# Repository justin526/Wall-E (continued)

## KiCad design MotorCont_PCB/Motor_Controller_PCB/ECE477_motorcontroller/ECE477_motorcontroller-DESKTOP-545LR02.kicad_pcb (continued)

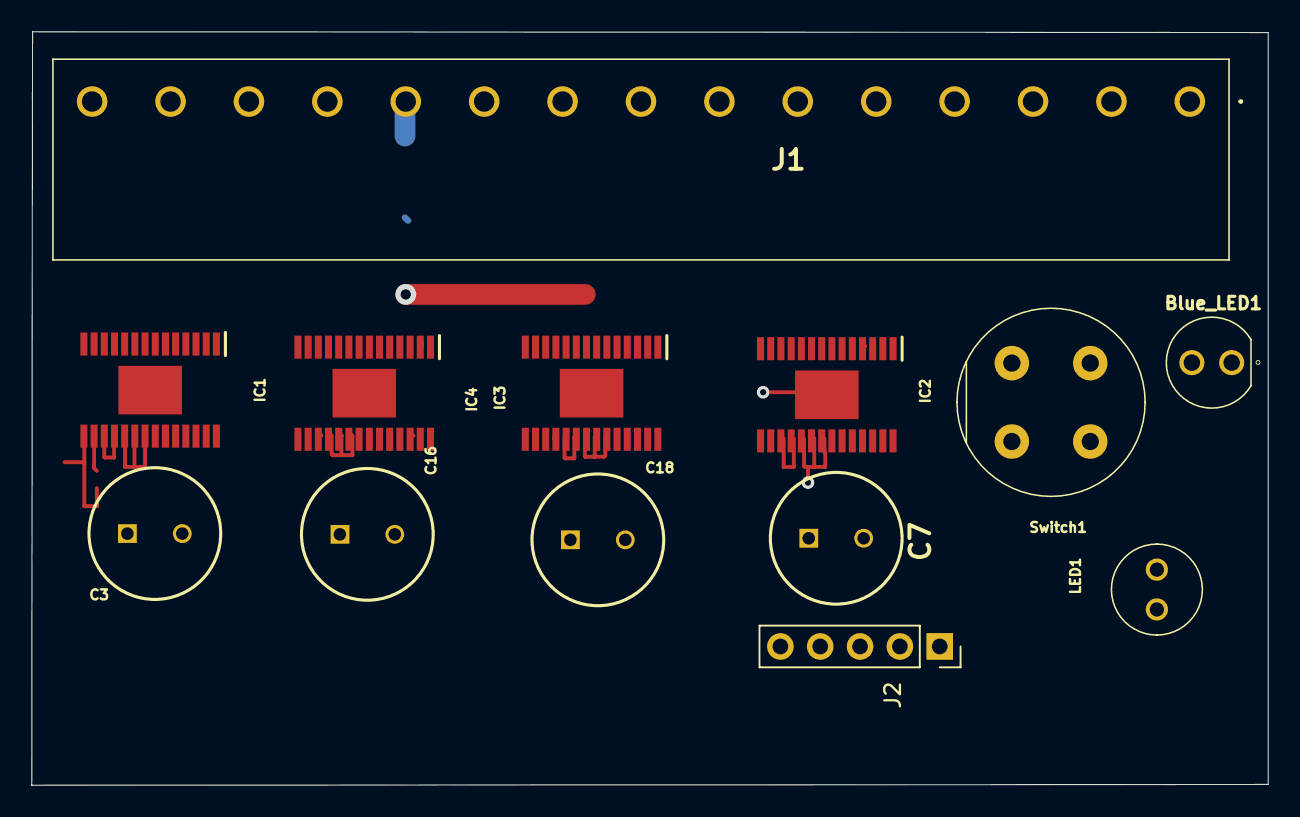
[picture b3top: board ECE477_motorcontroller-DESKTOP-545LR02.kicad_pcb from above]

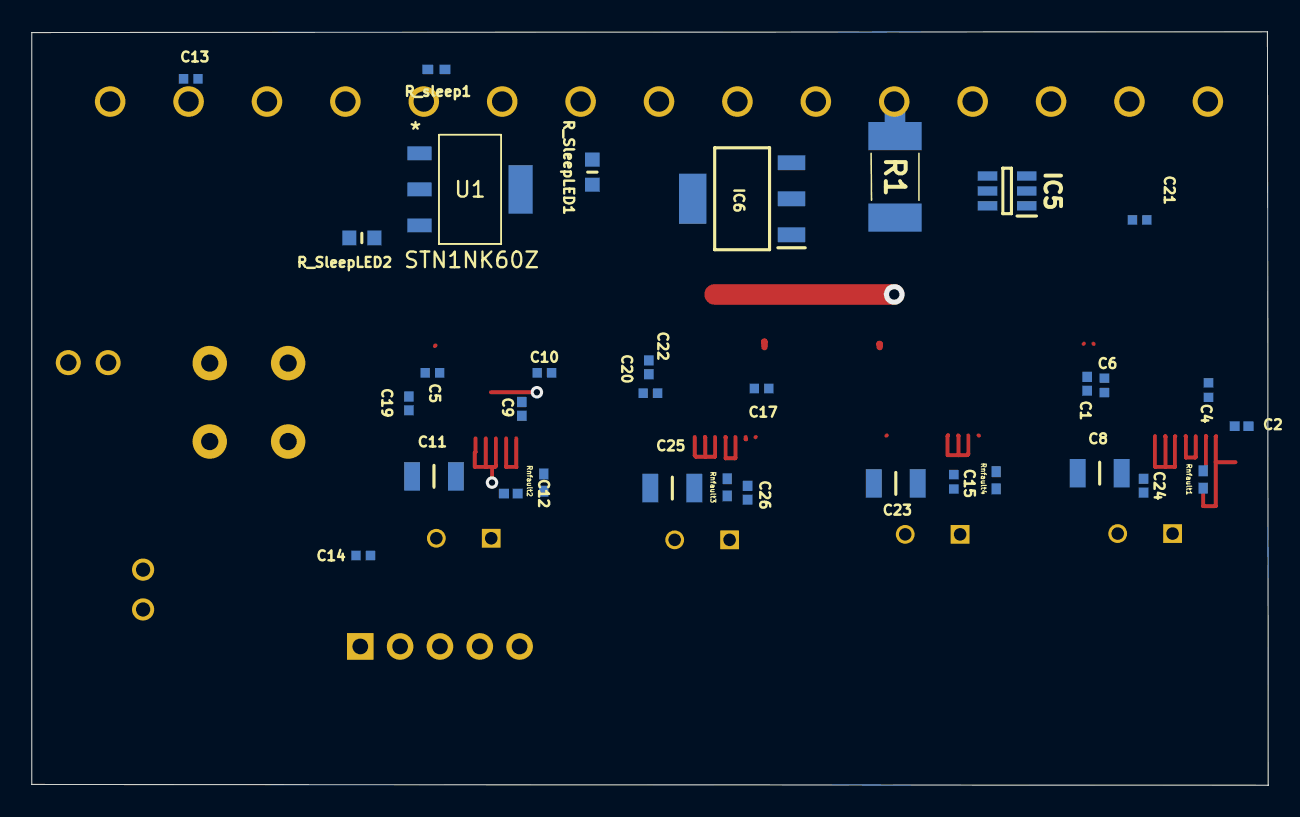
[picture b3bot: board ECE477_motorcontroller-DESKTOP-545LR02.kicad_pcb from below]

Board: 4 copper layers, 78.8 x 48.0 mm, 46 parts (33 on the bottom side), 43 nets.

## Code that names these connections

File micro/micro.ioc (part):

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Mcu.Name=STM32F446Z(C-E)Tx
Mcu.Package=LQFP144
Mcu.UserName=STM32F446ZETx
PA10.Mode=Asynchronous
PA10.Signal=USART1_RX
PA6.Signal=GPIO_Output
PA9.Mode=Asynchronous
PA9.Signal=USART1_TX
PB10.Mode=Asynchronous
PB10.Signal=USART3_TX
PB4.Signal=S_TIM3_CH1
PB5.Signal=S_TIM3_CH2
PB8.Signal=S_TIM2_CH1_ETR
PB9.Signal=S_TIM2_CH2
PC5.Mode=Asynchronous
PC5.Signal=USART3_RX
PE2.Signal=GPIO_Output
PE3.Signal=GPIO_Output
PE4.Signal=GPIO_Output
PE5.Signal=GPIO_Output
PE6.Signal=GPIO_Output
PE7.Mode=Asynchronous
PE7.Signal=UART5_RX
PE8.Mode=Asynchronous
PE8.Signal=UART5_TX
PF5.Signal=GPIO_Output
PF7.Mode=IN5
PF7.Signal=ADC3_IN5
RCC.SYSCLKFreq_VALUE=16000000
board=custom

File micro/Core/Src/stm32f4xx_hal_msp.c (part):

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
    __HAL_RCC_GPIOF_CLK_ENABLE();
    /**ADC3 GPIO Configuration
    PF7     ------> ADC3_IN5
    */
    GPIO_InitStruct.Pin = GPIO_PIN_7;
    GPIO_InitStruct.Mode = GPIO_MODE_ANALOG;
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    __HAL_RCC_ADC3_CLK_DISABLE();

    /**ADC3 GPIO Configuration
    PF7     ------> ADC3_IN5
    */
    HAL_GPIO_DeInit(GPIOF, GPIO_PIN_7);

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  /* USER CODE END TIM2_MspPostInit 0 */
    __HAL_RCC_GPIOB_CLK_ENABLE();
    /**TIM2 GPIO Configuration
    PB8     ------> TIM2_CH1
    PB9     ------> TIM2_CH2
    */
    GPIO_InitStruct.Pin = GPIO_PIN_8|GPIO_PIN_9;
    GPIO_InitStruct.Mode = GPIO_MODE_AF_PP;
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
    __HAL_RCC_GPIOB_CLK_ENABLE();
    /**TIM3 GPIO Configuration
    PB4     ------> TIM3_CH1
    PB5     ------> TIM3_CH2
    */
    GPIO_InitStruct.Pin = GPIO_PIN_4|GPIO_PIN_5;
    GPIO_InitStruct.Mode = GPIO_MODE_AF_PP;
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
    __HAL_RCC_GPIOE_CLK_ENABLE();
    /**UART5 GPIO Configuration
    PE7     ------> UART5_RX
    PE8     ------> UART5_TX
    */
    GPIO_InitStruct.Pin = GPIO_PIN_7|GPIO_PIN_8;
    GPIO_InitStruct.Mode = GPIO_MODE_AF_PP;
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
    __HAL_RCC_GPIOA_CLK_ENABLE();
    /**USART1 GPIO Configuration
    PA9     ------> USART1_TX
    PA10     ------> USART1_RX
    */
    GPIO_InitStruct.Pin = GPIO_PIN_9|GPIO_PIN_10;
    GPIO_InitStruct.Mode = GPIO_MODE_AF_PP;
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    __HAL_RCC_GPIOC_CLK_ENABLE();
    __HAL_RCC_GPIOB_CLK_ENABLE();
    /**USART3 GPIO Configuration
    PC5     ------> USART3_RX
    PB10     ------> USART3_TX
    */
    GPIO_InitStruct.Pin = GPIO_PIN_5;
    GPIO_InitStruct.Mode = GPIO_MODE_AF_PP;
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    __HAL_RCC_UART5_CLK_DISABLE();

    /**UART5 GPIO Configuration
    PE7     ------> UART5_RX
    PE8     ------> UART5_TX
    */
    HAL_GPIO_DeInit(GPIOE, GPIO_PIN_7|GPIO_PIN_8);

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    __HAL_RCC_USART1_CLK_DISABLE();

    /**USART1 GPIO Configuration
    PA9     ------> USART1_TX
    PA10     ------> USART1_RX
    */
    HAL_GPIO_DeInit(GPIOA, GPIO_PIN_9|GPIO_PIN_10);

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    __HAL_RCC_USART3_CLK_DISABLE();

    /**USART3 GPIO Configuration
    PC5     ------> USART3_RX
    PB10     ------> USART3_TX
    */
    HAL_GPIO_DeInit(GPIOC, GPIO_PIN_5);

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
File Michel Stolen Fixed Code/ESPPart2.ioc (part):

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Mcu.Name=STM32F407V(E-G)Tx
Mcu.Package=LQFP100
Mcu.UserName=STM32F407VGTx
PA0-WKUP.GPIOParameters=GPIO_PuPd,GPIO_Label,GPIO_ModeDefaultEXTI
PA0-WKUP.GPIO_Label=B1 [Blue PushButton]
PA0-WKUP.GPIO_ModeDefaultEXTI=GPIO_MODE_EVT_RISING
PA0-WKUP.GPIO_PuPd=GPIO_NOPULL
PA0-WKUP.Signal=GPXTI0
PA10.GPIOParameters=GPIO_Speed,GPIO_PuPd,GPIO_Label,GPIO_Mode
PA10.GPIO_Label=OTG_FS_ID
PA10.GPIO_Mode=GPIO_MODE_AF_PP
PA10.GPIO_PuPd=GPIO_NOPULL
PA10.GPIO_Speed=GPIO_SPEED_FREQ_LOW
PA10.Signal=USB_OTG_FS_ID
PA11.GPIOParameters=GPIO_Speed,GPIO_PuPd,GPIO_Label,GPIO_Mode
PA11.GPIO_Label=OTG_FS_DM
PA11.GPIO_Mode=GPIO_MODE_AF_PP
PA11.GPIO_PuPd=GPIO_NOPULL
PA11.GPIO_Speed=GPIO_SPEED_FREQ_LOW
PA11.Signal=USB_OTG_FS_DM
PA12.GPIOParameters=GPIO_Speed,GPIO_PuPd,GPIO_Label,GPIO_Mode
PA12.GPIO_Label=OTG_FS_DP
PA12.GPIO_Mode=GPIO_MODE_AF_PP
PA12.GPIO_PuPd=GPIO_NOPULL
PA12.GPIO_Speed=GPIO_SPEED_FREQ_LOW
PA12.Signal=USB_OTG_FS_DP
PA13.GPIOParameters=GPIO_Label
PA13.GPIO_Label=SWDIO
PA13.Mode=Serial_Wire
PA13.Signal=SYS_JTMS-SWDIO
PA14.GPIOParameters=GPIO_Label
PA14.GPIO_Label=SWCLK
PA14.Mode=Serial_Wire
PA14.Signal=SYS_JTCK-SWCLK
PA2.Mode=Asynchronous
PA2.Signal=USART2_TX
PA3.Mode=Asynchronous
PA3.Signal=USART2_RX
PA4.GPIOParameters=GPIO_Speed,GPIO_PuPd,GPIO_Label,GPIO_Mode
PA4.GPIO_Label=I2S3_WS [CS43L22_LRCK]
PA4.GPIO_Mode=GPIO_MODE_AF_PP
PA4.GPIO_PuPd=GPIO_NOPULL
PA4.GPIO_Speed=GPIO_SPEED_FREQ_LOW
PA4.Signal=I2S3_WS
PA5.GPIOParameters=GPIO_Speed,GPIO_PuPd,GPIO_Label,GPIO_Mode
PA5.GPIO_Label=SPI1_SCK [LIS302DL_SCL/SPC]
PA5.GPIO_Mode=GPIO_MODE_AF_PP
PA5.GPIO_PuPd=GPIO_NOPULL
PA5.GPIO_Speed=GPIO_SPEED_FREQ_LOW
PA5.Signal=SPI1_SCK
PA6.GPIOParameters=GPIO_Speed,GPIO_PuPd,GPIO_Label,GPIO_Mode
PA6.GPIO_Label=SPI1_MISO [LIS302DL_SDO]
PA6.GPIO_Mode=GPIO_MODE_AF_PP
PA6.GPIO_PuPd=GPIO_NOPULL
PA6.GPIO_Speed=GPIO_SPEED_FREQ_LOW
PA6.Signal=SPI1_MISO
PA7.GPIOParameters=GPIO_Speed,GPIO_PuPd,GPIO_Label,GPIO_Mode
PA7.GPIO_Label=SPI1_MOSI [LIS302DL_SDA/SDI/SDO]
PA7.GPIO_Mode=GPIO_MODE_AF_PP
PA7.GPIO_PuPd=GPIO_NOPULL
PA7.GPIO_Speed=GPIO_SPEED_FREQ_LOW
PA7.Signal=SPI1_MOSI
PA9.GPIOParameters=GPIO_PuPd,GPIO_Label,GPIO_Mode
PA9.GPIO_Label=VBUS_FS
PA9.GPIO_Mode=GPIO_MODE_INPUT
PA9.GPIO_PuPd=GPIO_NOPULL
PA9.Signal=USB_OTG_FS_VBUS
PB10.GPIOParameters=GPIO_Speed,GPIO_PuPd,GPIO_Label,GPIO_Mode
PB10.GPIO_Label=CLK_IN [MP45DT02_CLK]
PB10.GPIO_Mode=GPIO_MODE_AF_PP
PB10.GPIO_PuPd=GPIO_NOPULL
PB10.GPIO_Speed=GPIO_SPEED_FREQ_LOW
PB10.Signal=I2S2_CK
PB11.Mode=Asynchronous
PB11.Signal=USART3_RX
PB2.GPIOParameters=GPIO_PuPd,GPIO_Label,GPIO_Mode
PB2.GPIO_Label=BOOT1
PB2.GPIO_Mode=GPIO_MODE_INPUT
PB2.GPIO_PuPd=GPIO_NOPULL
PB2.Signal=GPIO_Input
PB3.GPIOParameters=GPIO_Label
PB3.GPIO_Label=SWO
PB3.Signal=SYS_JTDO-SWO
PB4.Signal=GPIO_Output
PB5.Signal=GPIO_Output
PB6.Signal=USART1_TX
PB7.Signal=USART1_RX
PB9.GPIOParameters=GPIO_Speed,GPIO_PuPd,GPIO_Label,GPIO_Pu,GPIO_Mode
PB9.GPIO_Label=Audio_SDA [CS43L22_SDA]
PB9.GPIO_Mode=GPIO_MODE_AF_OD
PB9.GPIO_Pu=GPIO_PULLUP
PB9.GPIO_PuPd=GPIO_NOPULL
PB9.GPIO_Speed=GPIO_SPEED_FREQ_LOW
PB9.Signal=I2C1_SDA
PC0.GPIOParameters=GPIO_Speed,PinState,GPIO_PuPd,GPIO_Label
PC0.GPIO_Label=OTG_FS_PowerSwitchOn
PC0.GPIO_PuPd=GPIO_NOPULL
PC0.GPIO_Speed=GPIO_SPEED_FREQ_LOW
PC0.PinState=GPIO_PIN_SET
PC0.Signal=GPIO_Output
PC10.GPIOParameters=GPIO_Speed,GPIO_PuPd,GPIO_Label,GPIO_Mode
PC10.GPIO_Label=I2S3_SCK [CS43L22_SCLK]
PC10.GPIO_Mode=GPIO_MODE_AF_PP
PC10.GPIO_PuPd=GPIO_NOPULL
PC10.GPIO_Speed=GPIO_SPEED_FREQ_LOW
PC10.Signal=I2S3_CK
PC12.GPIOParameters=GPIO_Speed,GPIO_PuPd,GPIO_Label,GPIO_Mode
PC12.GPIO_Label=I2S3_SD [CS43L22_SDIN]
PC12.GPIO_Mode=GPIO_MODE_AF_PP
PC12.GPIO_PuPd=GPIO_NOPULL
PC12.GPIO_Speed=GPIO_SPEED_FREQ_LOW
PC12.Signal=I2S3_SD
PC14-OSC32_IN.GPIOParameters=GPIO_Label
PC14-OSC32_IN.GPIO_Label=PC14-OSC32_IN
PC14-OSC32_IN.Mode=LSE-External-Oscillator
PC14-OSC32_IN.Signal=RCC_OSC32_IN
PC15-OSC32_OUT.GPIOParameters=GPIO_Label
PC15-OSC32_OUT.GPIO_Label=PC15-OSC32_OUT
PC15-OSC32_OUT.Mode=LSE-External-Oscillator
PC15-OSC32_OUT.Signal=RCC_OSC32_OUT
PC3.GPIOParameters=GPIO_Speed,GPIO_PuPd,GPIO_Label,GPIO_Mode
PC3.GPIO_Label=PDM_OUT [MP45DT02_DOUT]
PC3.GPIO_Mode=GPIO_MODE_AF_PP
PC3.GPIO_PuPd=GPIO_NOPULL
PC3.GPIO_Speed=GPIO_SPEED_FREQ_LOW
PC3.Signal=I2S2_SD
PC7.GPIOParameters=GPIO_Speed,GPIO_PuPd,GPIO_Label,GPIO_Mode
PC7.GPIO_Label=I2S3_MCK [CS43L22_MCLK]
PC7.GPIO_Mode=GPIO_MODE_AF_PP
PC7.GPIO_PuPd=GPIO_NOPULL
PC7.GPIO_Speed=GPIO_SPEED_FREQ_LOW
PC7.Signal=I2S3_MCK
PD12.GPIOParameters=GPIO_Speed,GPIO_PuPd,GPIO_Label
PD12.GPIO_Label=LD4 [Green Led]
PD12.GPIO_PuPd=GPIO_NOPULL
PD12.GPIO_Speed=GPIO_SPEED_FREQ_LOW
PD12.Signal=GPIO_Output
PD13.GPIOParameters=GPIO_Speed,GPIO_PuPd,GPIO_Label
PD13.GPIO_Label=LD3 [Orange Led]
PD13.GPIO_PuPd=GPIO_NOPULL
PD13.GPIO_Speed=GPIO_SPEED_FREQ_LOW
PD13.Signal=GPIO_Output
PD14.GPIOParameters=GPIO_Speed,GPIO_PuPd,GPIO_Label
PD14.GPIO_Label=LD5 [Red Led]
PD14.GPIO_PuPd=GPIO_NOPULL
PD14.GPIO_Speed=GPIO_SPEED_FREQ_LOW
PD14.Signal=GPIO_Output
PD15.GPIOParameters=GPIO_Speed,GPIO_PuPd,GPIO_Label
PD15.GPIO_Label=LD6 [Blue Led]
PD15.GPIO_PuPd=GPIO_NOPULL
PD15.GPIO_Speed=GPIO_SPEED_FREQ_LOW
PD15.Signal=GPIO_Output
PD4.GPIOParameters=GPIO_Speed,GPIO_PuPd,GPIO_Label
PD4.GPIO_Label=Audio_RST [CS43L22_RESET]
PD4.GPIO_PuPd=GPIO_NOPULL
PD4.GPIO_Speed=GPIO_SPEED_FREQ_LOW
PD4.Signal=GPIO_Output
PD5.GPIOParameters=GPIO_PuPd,GPIO_Label,GPIO_Mode
PD5.GPIO_Label=OTG_FS_OverCurrent
PD5.GPIO_Mode=GPIO_MODE_INPUT
PD5.GPIO_PuPd=GPIO_NOPULL
PD5.Signal=GPIO_Input
PD8.Mode=Asynchronous
PD8.Signal=USART3_TX
PE1.GPIOParameters=GPIO_PuPd,GPIO_Label,GPIO_ModeDefaultEXTI
PE1.GPIO_Label=MEMS_INT2 [LIS302DL_INT2]
PE1.GPIO_ModeDefaultEXTI=GPIO_MODE_EVT_RISING
PE1.GPIO_PuPd=GPIO_NOPULL
PE1.Signal=GPXTI1
PE3.GPIOParameters=GPIO_Speed,GPIO_PuPd,GPIO_Label
PE3.GPIO_Label=CS_I2C/SPI [LIS302DL_CS_I2C/SPI]
PE3.GPIO_PuPd=GPIO_NOPULL
PE3.GPIO_Speed=GPIO_SPEED_FREQ_LOW
PE3.Signal=GPIO_Output
PH0-OSC_IN.GPIOParameters=GPIO_Label
PH0-OSC_IN.GPIO_Label=PH0-OSC_IN
PH0-OSC_IN.Mode=HSE-External-Oscillator
PH0-OSC_IN.Signal=RCC_OSC_IN
PH1-OSC_OUT.GPIOParameters=GPIO_Label
PH1-OSC_OUT.GPIO_Label=PH1-OSC_OUT
PH1-OSC_OUT.Mode=HSE-External-Oscillator
PH1-OSC_OUT.Signal=RCC_OSC_OUT
RCC.HSE_VALUE=8000000
RCC.SYSCLKFreq_VALUE=168000000
RCC.SYSCLKSource=RCC_SYSCLKSOURCE_PLLCLK
board=STM32F407G-DISC1
boardIOC=true

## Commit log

2021-09-29 Stealing Viktor's Code
2021-10-01 Added UART + Servo Controller Code
2021-10-01 Moving parts into their separate directories
2021-10-01 Working arm code
2021-10-04 Added Schematic
2021-10-04 Added Symbol Library
2021-10-05 my stuff
2021-10-07 Finished hardcoding the arm data
2021-10-07 Pushing working arm code
2021-10-08 Finished with PCB model 1
2021-10-14 finished drc check
2021-10-14 Adding footprints/schematics locally
2021-10-14 Working more on footprint adjustments
2021-10-15 Archived main board
2021-10-15 Finalizing zipped main controller file
2021-10-15 Minor changes again
2021-10-15 Finally rescued footprints within the zip file - uploading to website now
2021-10-15 mounting holes and test points
2021-10-19 Increasing 5V Trace
2021-10-19 Final
2021-10-20 Almost approved
2021-10-20 Added V1 of MotorController Board
2021-10-22 final changes to pcb
2021-10-23 Finishing up small airwires
2021-10-27 Integration
2021-11-17 new code
2021-11-18 gui plus micro
2021-12-03 final code
2021-12-03 final GUI
2021-12-09 gui again
2021-12-14 This is the final commit for all the micrcontroller code.This include a communication to Mohamed's phone and updated servo code.
2021-12-15 Refactoring
2021-12-15 Refactor
2021-12-15 Refactor3
